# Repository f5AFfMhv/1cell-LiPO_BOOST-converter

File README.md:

# 1 cell LiPO battery voltage BOOST converter board

Designed with KiCAD.
<br>
[Schematic](https://github.com/f5AFfMhv/1cell-LiPO_BOOST-converter/raw/master/schematic.pdf)
<br>
[BOM](https://github.com/f5AFfMhv/1cell-LiPO_BOOST-converter/raw/master/1Cell_LiPO_BOOST_converter.csv)

## Features

<ul>
  <li>Boost converter based on <a href="http://ww1.microchip.com/downloads/en/DeviceDoc/20005315B.pdf">MCP1661</a>.</li>
  <li>One cell LiPO battery charger based on <a href="http://ww1.microchip.com/downloads/en/DeviceDoc/20001984g.pdf">MCP73831</a>.</li>
  <li>Adjustable low input voltage indication.</li>
  <li>All three parts of the circuit can be cut out of the board and used seperately.</li>
</ul>

## Rev B

<ul>
  <li>Fixed LiPO charger indicator LED polarity.</li>
</ul>

## Board pictures

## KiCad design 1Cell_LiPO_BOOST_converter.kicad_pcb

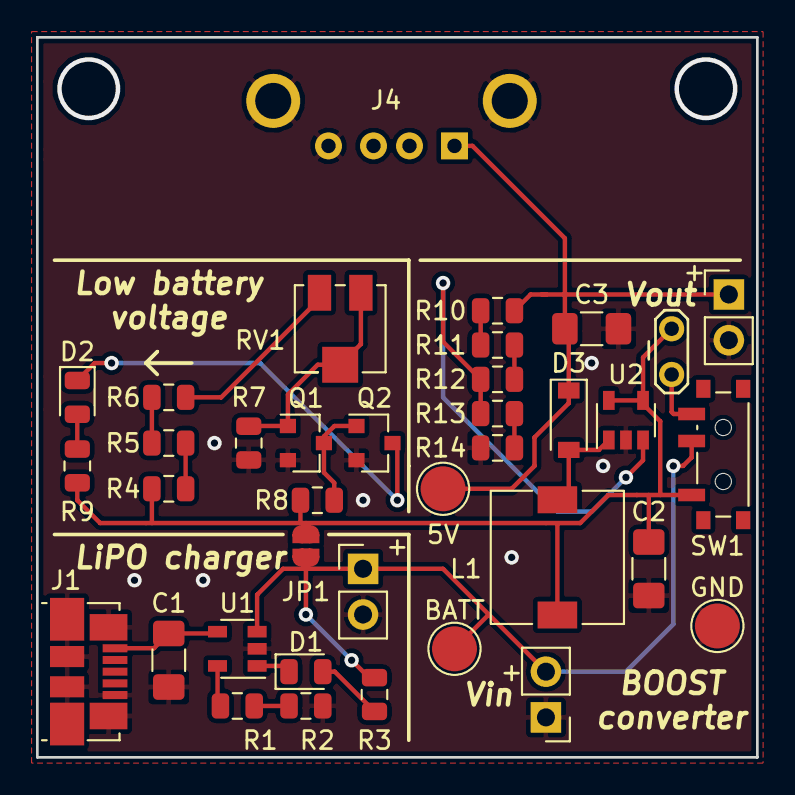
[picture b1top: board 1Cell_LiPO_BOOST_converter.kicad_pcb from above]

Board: 2 copper layers, 40.0 x 40.0 mm, 37 parts (0 on the bottom side), 22 nets.

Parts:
5V: +5V; TestPoint_Pad_D2.5mm
+: LiPo; PinHeader_1x02_P2.54mm_Vertical
+#2: Vin; PinHeader_1x02_P2.54mm_Vertical
+#3: Vout; PinHeader_1x02_P2.54mm_Vertical
BATT: LiPO; TestPoint_Pad_D2.5mm
C1, C2, C3: 10u; C_1206_3216Metric_Pad1.42x1.75mm_HandSolder
D1, D2: LED; LED_0805_2012Metric
D3: MBR0530; D_SOD-123
GND: GND; TestPoint_Pad_D2.5mm
I: Current; TestPoint_2Pads_Pitch2.54mm_Drill0.8mm
J1: microUSB; USB_Micro-B_Molex_47346-0001
J4: USB_A; USB_A_THT
JP1: SJ_O; SolderJumper-2_P1.3mm_Open_RoundedPad1.0x1.5mm
L1: 4.7u; L_7.3x7.3_H4.5
Q1, Q2: BC847; SOT-23
R1, R2, R3, R9: 1K; R_0805_2012Metric
R4: 33K; R_0805_2012Metric
R5, R6, R7: 10K; R_0805_2012Metric
R8, R13, R14: 47K; R_0805_2012Metric
R10, R11, R12: 100K; R_0805_2012Metric
RV1: 10K; Potentiometer_Bourns_3214J_Horizontal
SW1: ON/OFF; SW_SPDT_PCM12
U1: MCP73831; SOT-23-5
U2: MCP1661; SOT-23-5

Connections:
+5V: 5V.1, +#3.1, C3.1, D3.1, J4.1, R10.1
+BATT: C2.1, I.2, JP1.1, L1.1, R4.1, R8.1, R9.1, SW1.1, U2.4, U2.5
GND: +.1, +#2.2, +#3.2, C1.2, C2.2, C3.2, GND.1, J1.5, J1.6, J4.4, J4.5, Q1.2, Q2.2, R2.2, R7.2, R14.2, U1.2, U2.2
unnamed: +.2, +#2.1, BATT.1, JP1.2, R3.1, SW1.2, U1.3
unnamed: C1.1, J1.1, U1.4
unnamed: D1.1, U1.1
unnamed: D1.2, R3.2
unnamed: D2.1, Q2.3
unnamed: D2.2, R9.2
unnamed: D3.2, L1.2, U2.1
unnamed: I.1, SW1.3
unnamed: Q1.1, R7.1, RV1.2, RV1.3
unnamed: Q1.3, Q2.1, R8.2
unnamed: R1.1, U1.5
unnamed: R1.2, R2.1
unnamed: R4.2, R5.1
unnamed: R5.2, R6.1
unnamed: R6.2, RV1.1
unnamed: R10.2, R11.1
unnamed: R11.2, R12.1
unnamed: R12.2, R13.1, U2.3
unnamed: R13.2, R14.1

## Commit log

2019-02-03 added 3D images
2019-02-03 added schematic pdf
2019-03-03 Added Rev B
